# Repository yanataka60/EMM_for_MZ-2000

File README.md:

# EMMボード for MZ-2000

　MZ-2000、MZ-2200、MZ-80B、MZ-2500(2000モード、80Bモード)用の512K S-RAM EMMボードを作ってみました。

　特徴としては、

　1)I/Oポートは、I・Oデータ機器 PIO-3034互換なのでそのままPIO-3034(320K EMM)として使えます。

　2)CR-2032のバックアップにより電源を切ってもメモリ内容が保持されます。(Rev1.5のバックアップ期間は計算上数年は大丈夫です。)

　3)スイッチにより書込み禁止にできます。

　4)I/Oポートから直接EMMを読み書きすれば512K外部RAMとして使えます。

　5)MZ-2000_SDと併用すれば512KまるごとSDカードからLOAD、SAVEが可能です。

　6)ジャンパによりEMM0～EMM3のいずれかに設定して使えます。(MZ-2000_SDと併用するときはEMM0としては使えません。EMM1～EMM3として使ってください。)

　7)おまけでアドレスカウンタリセットを付けました。

　なお、MZ-2000、MZ-2200、MZ-80B、MZ2500本体の通常の電源ON/OFFでの正常動作は確認していますが、電源ON/OFFを瞬間的に繰り返すような無理な使い方をするとEMMのバックアップが正常に動作しないことがあります。電源ON/OFFを瞬間的に繰り返すと電源ユニットにもダメージが及ぶこともあるので電源ON/OFFは間をおいて行ってください。

## 回路図
　KiCadフォルダ内にEMMとEMM&CMUの２種類があります。CMU-800を接続するにはCMU-800から出ているフラットケーブルのカードエッジコネクタを接続する必要があり、CMU-800所有者がスロット不足に悩まなくて済むようカードエッジをつけ足したもので回路は全く同じものです。

　お好きな方を使ってください。

[回路図](https://github.com/yanataka60/EMM_for_MZ-2000/blob/main/Kicad/EMM/MZ-2000_EMM.pdf)

[回路図](https://github.com/yanataka60/EMM_for_MZ-2000/blob/main/Kicad/EMM%26CMU/MZ-2000_EMM_CMU.pdf)

## 部品表
|番号|品名|数量|備考|
| ------------ | ------------ | ------------ | ------------ |
|C1-C15|積層セラミックコンデンサ 0.1uF|15||
|C16|積層セラミックコンデンサ 220pF|1||
|C17|電解コンデンサ 100uF|1||
|D1-D2|ダイオード 1N4148|2|1S4から1N4148に変更|
|Q1|FET 2N7000|1||
|R1|カーボン抵抗 100Ω|1||
|R2|カーボン抵抗 1k|1||
|R3|カーボン抵抗 10k|1||
|S1,S2|3Pスライドスイッチ又は1x3ピンヘッダとジャンパーピン|2|秋月電子通商 SS12D01G4又はPH-1X3SG,MJ-254-6BK等|
|S3|3Pスライドスイッチ|1|秋月電子通商 SS12D01G4|
|U1,U2|74LS04|2|樫木総業等|
|U3|74LS14|1|樫木総業等|
|U4,U15|74LS245|2|樫木総業等|
|U5|74LS30|1|樫木総業等|
|U6-U10|74LS193|5|樫木総業等|
|U11,U12|74LS138|2|樫木総業等|
|U13|SRAM HM628512|1|注1)|
|U14|74LS11|1|樫木総業等|
|BT1|ボタン電池基板取付用ホルダー CR2032用(小型タイプ)|1|秋月電子通商 CH25-2032LFなど|

注1)DIPで設計しています。SOPを入手した場合にはこちらの変換基板を使うことで装着できます。

https://github.com/yanataka60/SOPtoDIP32

## I/Oポート
### EMM0
ジャンパピンA3、A2とも0の位置にします。

#### 注)EMM0の設定ではMZ-2000_SDと共存できません。MZ-2000_SDと共存させたい場合は、EMM1～EMM3の設定で使ってください。

|アドレス|R/W|説明|
| ------------ | ------------ | ------------ |
|A0h|R|アドレスカウンタリセット|
|A0h|W|アドレスカウンタ Bit[7:0]|
|A1h|W|アドレスカウンタ Bit[15:8]|
|A2h|W|アドレスカウンタ Bit[18:16]|
|A3h|R|データ読み出し:アドレスカウンタ+1|
|A3h|W|データ書き込み:アドレスカウンタ+1|
### EMM1
ジャンパピンA3を0、A2を1の位置にします。

|アドレス|R/W|説明|
| ------------ | ------------ | ------------ |
|A4h|R|アドレスカウンタリセット|
|A4h|W|アドレスカウンタ Bit[7:0]|
|A5h|W|アドレスカウンタ Bit[15:8]|
|A6h|W|アドレスカウンタ Bit[18:16]|
|A7h|R|データ読み出し:アドレスカウンタ+1|
|A7h|W|データ書き込み:アドレスカウンタ+1|
### EMM2
ジャンパピンA3を1、A2を0の位置にします。

|アドレス|R/W|説明|
| ------------ | ------------ | ------------ |
|A8h|R|アドレスカウンタリセット|
|A8h|W|アドレスカウンタ Bit[7:0]|
|A9h|W|アドレスカウンタ Bit[15:8]|
|AAh|W|アドレスカウンタ Bit[18:16]|
|ABh|R|データ読み出し:アドレスカウンタ+1|
|ABh|W|データ書き込み:アドレスカウンタ+1|
### EMM3
ジャンパピンA3、A2とも1の位置にします。

|アドレス|R/W|説明|
| ------------ | ------------ | ------------ |
|ACh|R|アドレスカウンタリセット|
|ACh|W|アドレスカウンタ Bit[7:0]|
|ADh|W|アドレスカウンタ Bit[15:8]|
|AEh|W|アドレスカウンタ Bit[18:16]|
|AFh|R|データ読み出し:アドレスカウンタ+1|
|AFh|W|データ書き込み:アドレスカウンタ+1|

## SAMPLEプログラム
　SAMPLEフォルダ内にEMMANIME、EMMMENU、EMMCHECK、EMMTESTを置きました。

　使い方については、各フォルダ内のREADME.mdを参照してください。

## EMMからの起動
　せっかくバッテリーバックアップに対応させたのでMZ-2000_SDの起動時にEMMから起動できるようにしてみました。

　MZ-2000_SDのROMをEMM対応BOOT LOADERに書き換える必要があります。

　MZ-2000_SDの「EMMボード for MZ-2000からの起動」を参照してください。

　https://github.com/yanataka60/MZ-2000_SD?tab=readme-ov-file#emm%E3%83%9C%E3%83%BC%E3%83%89-for-mz-2000%E3%81%8B%E3%82%89%E3%81%AE%E8%B5%B7%E5%8B%95

## 初期基板をバッテリーバックアップ対応とするには
#### 2026.2.16 Rev1.5基板ではバックアップ時間が飛躍的に増加し、ICに負荷をかけない回路となりました。バッテリーバックアップを使うなら出来ればRev1.5基板に更新してください。

　以下に示すパターンカット、ジャンパ、追加部品(抵抗10k×1本、ダイオード1S4×1本)で改造することで初期基板をバッテリーバックアップ対応とすることが可能です。

　ただし、パターンカット個所がU2 74LS04 ICソケット内側にもあるのでEMMボード組み立て済みの場合にはICソケットを一旦取り外す必要があります。

　また、EMM基板とEMM&CMU基板ではパターンカットの個所が若干違いがあります。ジャンパは共通です。

### EMM基板パターンカット個所
　U2 74LS04の3Pin、5Pin、9Pin、11PinをGNDから切り離します。

　U13 HM628512の29PinとU14 74LS11 13Pinとの接続をカットします。

　U13 HM628512の22、24Pin、R2 抵抗 10Kとの接続点とU12 74LS138 5Pinとの接続をカットします。

部品面全体
.JPG)

部品面拡大1
.JPG)

部品面拡大2
.JPG)

ハンダ面全体
.jpg)

ハンダ面拡大1
.JPG)

ハンダ面拡大2
.JPG)

### EMM&CMU基板パターンカット個所
　切り離すポイントはEMM基板と同じですが、基板上のカット位置は若干異なります。

部品面全体
.JPG)

部品面拡大1
.JPG)

ハンダ面全体
.JPG)

ハンダ面拡大1
.JPG)

ハンダ面拡大2
.JPG)

### ジャンパ個所
　U12 74LS138 5PinとU2 74LS04 3Pin

　U2 74LS04 4Pinと5Pin

　U2 74LS04 6PinとU13 HM628512 24Pin

　U12 74LS138 12PinとU2 74LS04 11Pin

　U2 74LS04 10Pinと9Pin

　U2 74LS04 8Pinとダイオード 1S4 アノード

　ダイオード 1S4 カソードとU13 HM628512 29Pin

　U13 HM628512 29Pinと抵抗 10KとU13 HM628512 32Pin

ハンダ面全体
.JPG)

ハンダ面拡大1
.JPG)

ハンダ面拡大2
.JPG)

## 追記
2025.12.20 SAMPLEプログラムを追加しました。

2025.12.23 EMMLOAD、EMMSAVEを統合し、EMMMENUとしました。

2025.12.23 EMMANIME2000、EMMANIME80Bを統合し、EMMANIMEとしました。

2025.12.27 EMMMENUにSDアクセスルーチンを内包しました。

2025.12.28 バッテリーバックアップしていてもメモリ内容が変わってしまう症状が時々発生しています。原因と対策を検討中です。

2026.1.1 簡単な修正では症状を抑えることが出来ないのでこのバージョンではバッテリーバックアップは断念し、対策を練りなおします。

2026.1.22 バッテリーバックアップ正常版(Rev1.2)に更新。初期基板をバッテリーバックアップ対応とするための改修方法を記述。

2026.1.23 バックアップ期間について追記。

2026.1.24 HM628512の書き込み時WE信号が瞬間的に5.9Vほどの電圧が掛かることを記述。すーぱーたーぼさんご指摘ありがとうございました。

2026.1.25 D1,D2を1S4から1N4148に変更。AIGOU Yoshiakiさんアドバイスありがとうございました。

2026.2.16 すーぱーたーぼさんに提案していただいていたn-FETを用いたバッテリーバックアップ回路を採用しました。すーぱーたーぼさんアドバイスありがとうございました。

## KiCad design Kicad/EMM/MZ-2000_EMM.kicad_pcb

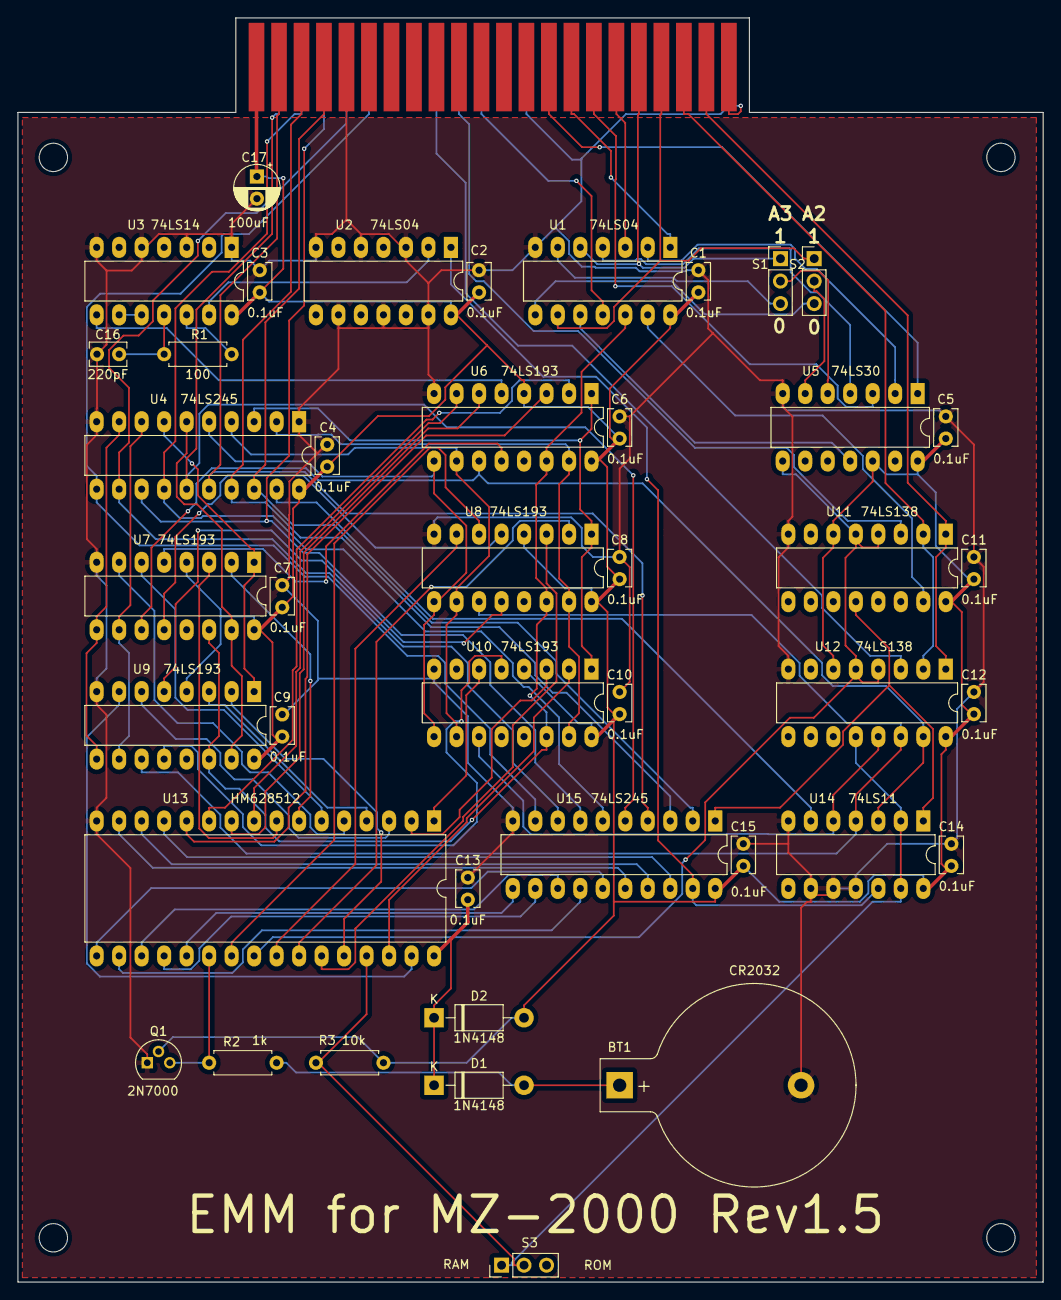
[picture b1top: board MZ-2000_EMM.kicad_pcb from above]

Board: 2 copper layers, 115.8 x 142.7 mm, 47 parts (0 on the bottom side), 86 nets.

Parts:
BT1: Battery_Cell; BatteryHolder_Keystone_103_1x20mm
C1, C2, C3, C4, C5, C6, C7, C8, C9, C10, C11, C12, C13, C14, C15: 0.1uF; C_Rect_L4.0mm_W2.5mm_P2.50mm
C16: 220pF; C_Rect_L4.0mm_W2.5mm_P2.50mm
C17: 100uF; CP_Radial_D5.0mm_P2.50mm
D1, D2: 1N4148; D_DO-41_SOD81_P10.16mm_Horizontal
J1: Conn_02x22_Row_Letter_First; BUS_MZ2000
MH1, MH2, MH3, MH4: MountingHole_3.2mm_M3
Q1: 2N7000; TO-92
R1: 100; R_Axial_DIN0207_L6.3mm_D2.5mm_P7.62mm_Horizontal
R2: 1K; R_Axial_DIN0207_L6.3mm_D2.5mm_P7.62mm_Horizontal
R3: 10K; R_Axial_DIN0207_L6.3mm_D2.5mm_P7.62mm_Horizontal
S1: A3_select; PinHeader_1x03_P2.54mm_Vertical
S2: A2_select; PinHeader_1x03_P2.54mm_Vertical
S3: SLIDE_SWITCH_3P; PinHeader_1x03_P2.54mm_Vertical
U1, U2: 74LS04; DIP-14_W7.62mm_LongPads
U3: 74LS14; DIP-14_W7.62mm_LongPads
U4, U15: 74LS245; DIP-20_W7.62mm_LongPads
U5: 74LS30; DIP-14_W7.62mm_LongPads
U6, U7, U8, U9, U10: 74LS193; DIP-16_W7.62mm_LongPads
U11, U12: 74LS138; DIP-16_W7.62mm_LongPads
U13: HM628512LFP-5; DIP-32_W15.24mm_LongPads
U14: 74LS11; DIP-14_W7.62mm_LongPads

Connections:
+5V: C1.1, C2.1, C3.1, C4.1, C5.1, C6.1, C7.1, C8.1, C9.1, C10.1, C11.1, C12.1, C14.1, C15.1, C17.1, D2.2, J1.a1, J1.b1, Q1.2, R3.2, U1.14, U2.14, U3.14, U4.20, U5.12, U5.14, U6.4, U6.16, U7.4, U7.16, U8.4, U8.16, U9.4, U9.16, U10.4, U10.16, U11.6, U11.16, U12.6, U12.16, U14.14, U15.20
/A0: J1.a21, U11.1, U12.1
/A1: J1.a20, U11.2, U12.2
/A2: J1.a19, S2.1, U1.9
/A3: J1.a18, S1.1, U1.5
/A4: J1.a17, U1.3
/A5: J1.a16, U5.3
/A6: J1.a15, U1.1
/A7: J1.a14, U5.1
/D0: J1.a4, U4.18, U15.2
/D1: J1.a3, U4.17, U15.3
/D2: J1.a2, U4.16, U15.4
/D3: J1.b2, U4.15, U15.5
/D4: J1.b3, U4.14, U15.6
/D5: J1.b4, U4.13, U15.7
/D6: J1.b5, U4.12, U15.8
/D7: J1.b6, U4.11, U15.9
/x0_RD: U1.13, U11.15
/x0_WR: U6.11, U7.11, U12.15, U14.3
/x1_WR: U8.11, U9.11, U12.14, U14.4
/x2_WR: U10.11, U12.13, U14.5
/x3_RD: U11.12, U14.1, U15.1
/x3_WR: S3.1, U12.12, U14.2, U14.13
/~IOREQ: J1.b11, U1.11
/~RD: J1.b10, U11.3
/~WR: J1.b9, U12.3
GND: BT1.2, C1.2, C2.2, C3.2, C4.2, C5.2, C6.2, C7.2, C8.2, C9.2, C10.2, C11.2, C12.2, C13.2, C14.2, C15.2, C16.2, C17.2, J1.a5, J1.a22, J1.b13, J1.b22, Q1.1, U1.7, U2.3, U2.5, U2.7, U2.9, U2.11, U2.13, U3.1, U3.3, U3.5, U3.7, U4.1, U4.10, U5.7, U6.8, U7.8, U8.8, U9.8, U10.8, U11.8, U12.8, U13.16, U14.7, U14.9, U14.10, U14.11, U15.10
unnamed: BT1.1, D1.2, R2.2
unnamed: C13.1, D1.1, D2.1, U13.32
unnamed: C16.1, R1.2, U3.11
unnamed: Q1.3, R2.1, U13.22
unnamed: R1.1, U3.12
unnamed: R3.1, S3.2, U13.29
unnamed: S1.2, U5.5
unnamed: S1.3, U1.6
unnamed: S2.2, U5.6
unnamed: S2.3, U1.8
unnamed: U1.2, U5.2
unnamed: U1.4, U5.4
unnamed: U1.10, U5.11
unnamed: U1.12, U6.14, U7.14, U8.14, U9.14, U10.14
unnamed: U2.2, U3.13
unnamed: U3.8, U6.5
unnamed: U3.9, U3.10
unnamed: U4.6, U7.15, U9.15
unnamed: U4.7, U7.1, U9.1
unnamed: U4.8, U7.10, U9.10
unnamed: U4.9, U7.9, U9.9
unnamed: U6.12, U7.5
unnamed: U7.12, U8.5
unnamed: U8.12, U9.5
unnamed: U4.3, U6.1, U8.1, U10.1
unnamed: U10.2, U13.30
unnamed: U10.3, U13.2
unnamed: U9.12, U10.5
unnamed: U10.6, U13.1
unnamed: U4.5, U6.9, U8.9, U10.9
unnamed: U4.4, U6.10, U8.10, U10.10
unnamed: U4.2, U6.15, U8.15, U10.15
unnamed: U5.8, U11.4, U11.5, U12.4, U12.5, U13.24
unnamed: U9.6, U13.3
unnamed: U9.3, U13.4
unnamed: U7.7, U13.5
unnamed: U7.6, U13.6
unnamed: U7.2, U13.7
unnamed: U7.3, U13.8
unnamed: U6.7, U13.9
unnamed: U6.6, U13.10
unnamed: U6.2, U13.11
unnamed: U6.3, U13.12
unnamed: U13.13, U15.18
unnamed: U13.14, U15.17
unnamed: U13.15, U15.16
unnamed: U13.17, U15.15
unnamed: U13.18, U15.14
unnamed: U13.19, U15.13
unnamed: U13.20, U15.12
unnamed: U13.21, U15.11
unnamed: U8.6, U13.23
unnamed: U8.7, U13.25
unnamed: U8.2, U13.26
unnamed: U8.3, U13.27
unnamed: U9.2, U13.28
unnamed: U9.7, U13.31
unnamed: U4.19, U14.6
unnamed: U2.1, U14.12, U15.19
